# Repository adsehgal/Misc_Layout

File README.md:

<!--  -->

# \*\*

## _Requirements:_

-

## Built With

- [KiCad](https://kicad-pcb.org/) - Schematic capture and layout
- [VS Code](https://code.visualstudio.com/) - Used to develop firmware
- [Fusion 360](https://www.autodesk.com/education/edu-software/overview) - Used to design 3-D models for packages

### _Notes:_

## Authors

- **Aditya Sehgal** - _PCB Layout, Firmware, 3-D Modelling_ - [Adsehgal](https://github.com/adsehgal)

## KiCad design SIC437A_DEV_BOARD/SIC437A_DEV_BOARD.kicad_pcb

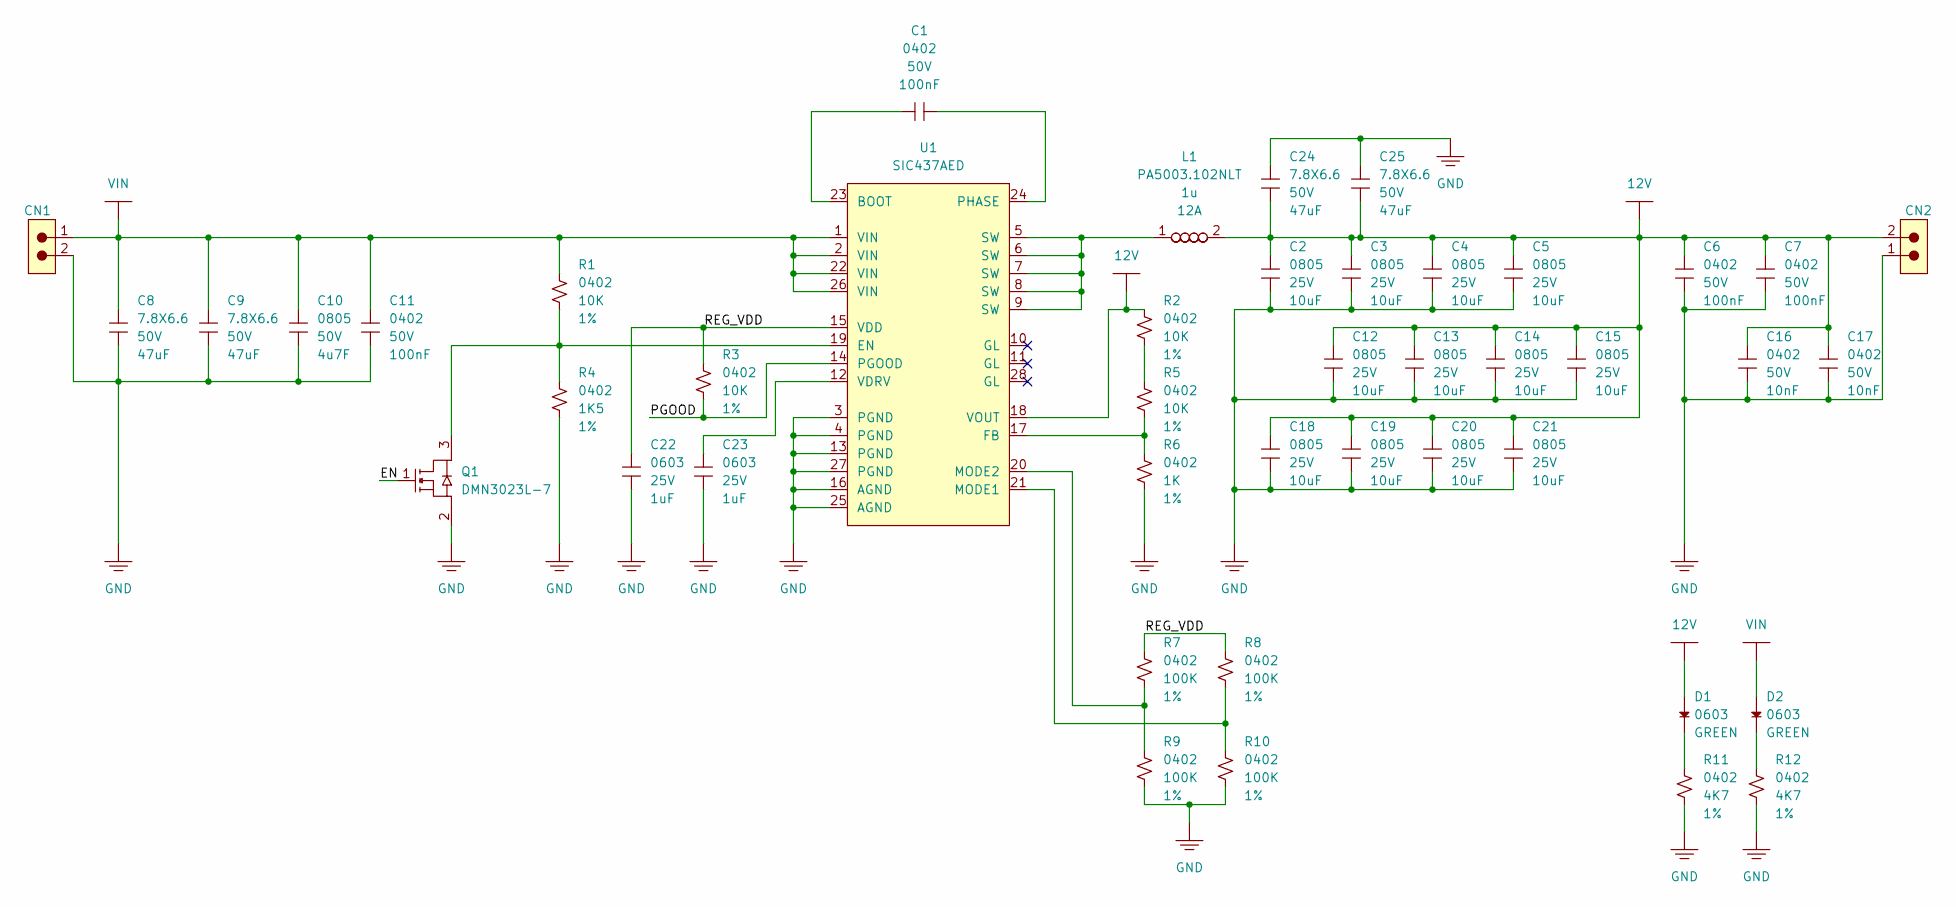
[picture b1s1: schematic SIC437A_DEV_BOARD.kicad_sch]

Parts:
C1, C6, C7, C11: Cap_100n_50V_0402; CAP_0402_LEAST; Voltage 50V; Tolerance 10%
C2, C3, C4, C5, C12, C13, C14, C15, C18, C19, C20, C21: Cap_10u_25V_0805; CAP_0805_LEAST; Voltage 25V; Tolerance 10%
C8, C9, C24, C25: Cap_47u_50V_7.8X6.6; CAP_STACK_7.8X6.6; Voltage 50V; Tolerance 20%
C10: Cap_4u7_50V_0805; CAP_0805_LEAST; Voltage 50V; Tolerance 10%
C16, C17: Cap_10n_50V_0402; CAP_0402_LEAST; Voltage 50V; Tolerance 5%
C22, C23: Cap_1u_25V_0603; CAP_0603_LEAST; Voltage 25V; Tolerance 10%
CN1, CN2: DATAMATE_2P_RA_M80-5000000M5-02-333-00-000
D1, D2: LED_GREEN_0603; LED_0603_LEAST
L1: PA5003.102NLT; IND_5.5X5.3
Q1: DMN3023L-7; SOT23_3
R1, R2, R3, R5: Res_10K_0402; RES_0402_LEAST; Tolerance 1%
R4: Res_1K5_0402; RES_0402_LEAST; Tolerance 1%
R6: Res_1K_0402; RES_0402_LEAST; Tolerance 1%
R7, R8, R9, R10: Res_100K_0402; RES_0402_LEAST; Tolerance 1%
R11, R12: Res_4K7_0402; RES_0402_LEAST; Tolerance 1%
U1: SIC437AED; MLP44_24L

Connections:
12V: C2.2, C3.2, C4.2, C5.2, C6.2, C7.2, C12.2, C13.2, C14.2, C15.2, C16.2, C17.2, C18.2, C19.2, C20.2, C21.2, C24.1, C25.1, CN2.2 (PA), D1.2, L1.2, R2.2, U1.18 (VOUT)
/EN: Q1.1
/PGOOD: R3.1, U1.14 (PGOOD)
/REG_VDD: C22.2, R3.2, R7.2, R8.2, U1.15 (VDD)
GND: C2.1, C3.1, C4.1, C5.1, C6.1, C7.1, C8.1, C9.1, C10.1, C11.1, C12.1, C13.1, C14.1, C15.1, C16.1, C17.1, C18.1, C19.1, C20.1, C21.1, C22.1, C23.1, C24.2, C25.2, CN1.2 (PA), CN2.1 (PA), Q1.2, R4.1, R6.1, R9.1, R10.1, R11.1, R12.1, U1.3 (PGND), U1.4 (PGND), U1.13 (PGND), U1.16 (AGND), U1.25 (AGND), U1.27 (PGND)
unnamed: C1.1, U1.23 (BOOT)
unnamed: C1.2, U1.24 (PHASE)
unnamed: C23.2, U1.12 (VDRV)
unnamed: D1.1, R11.2
unnamed: D2.1, R12.2
unnamed: L1.1, U1.5 (SW), U1.6 (SW), U1.7 (SW), U1.8 (SW), U1.9 (SW)
unnamed: Q1.3, R1.1, R4.2, U1.19 (EN)
unnamed: R2.1, R5.2
unnamed: R5.1, R6.2, U1.17 (FB)
unnamed: R7.1, R9.2, U1.20 (MODE2)
unnamed: R8.1, R10.2, U1.21 (MODE1)
VIN: C8.2, C9.2, C10.2, C11.2, CN1.1 (PA), D2.2, R1.2, U1.1 (VIN), U1.2 (VIN), U1.22 (VIN), U1.26 (VIN)

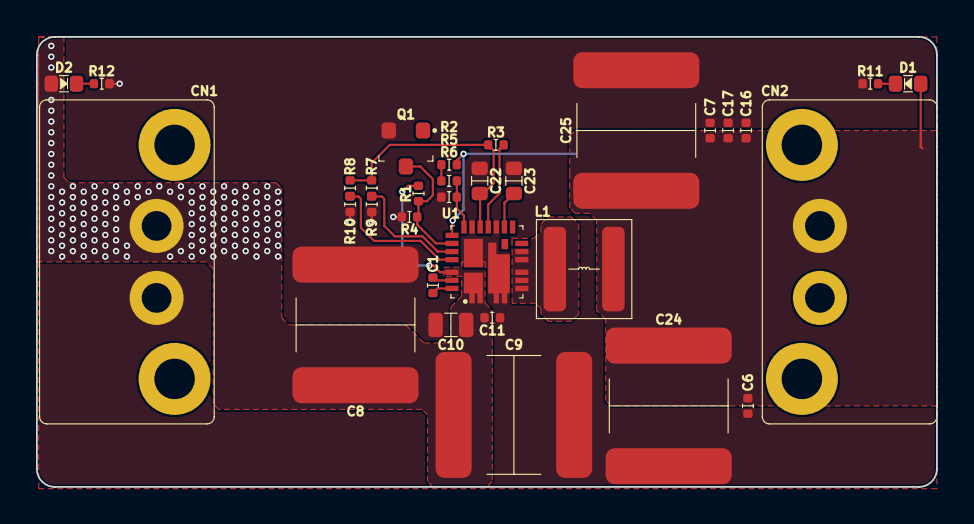
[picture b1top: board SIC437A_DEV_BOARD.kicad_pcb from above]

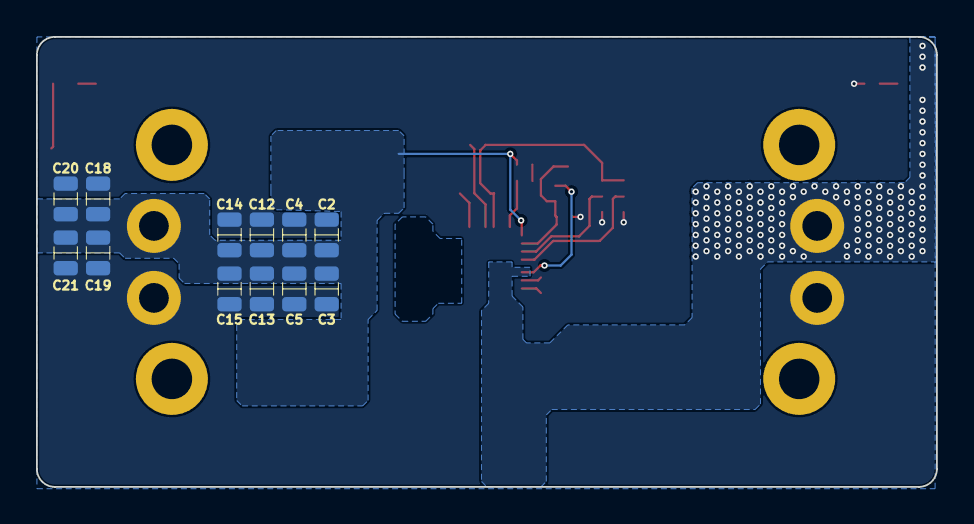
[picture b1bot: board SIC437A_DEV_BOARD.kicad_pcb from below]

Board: 4 copper layers, 50.0 x 25.0 mm, 44 parts (12 on the bottom side), 16 nets.

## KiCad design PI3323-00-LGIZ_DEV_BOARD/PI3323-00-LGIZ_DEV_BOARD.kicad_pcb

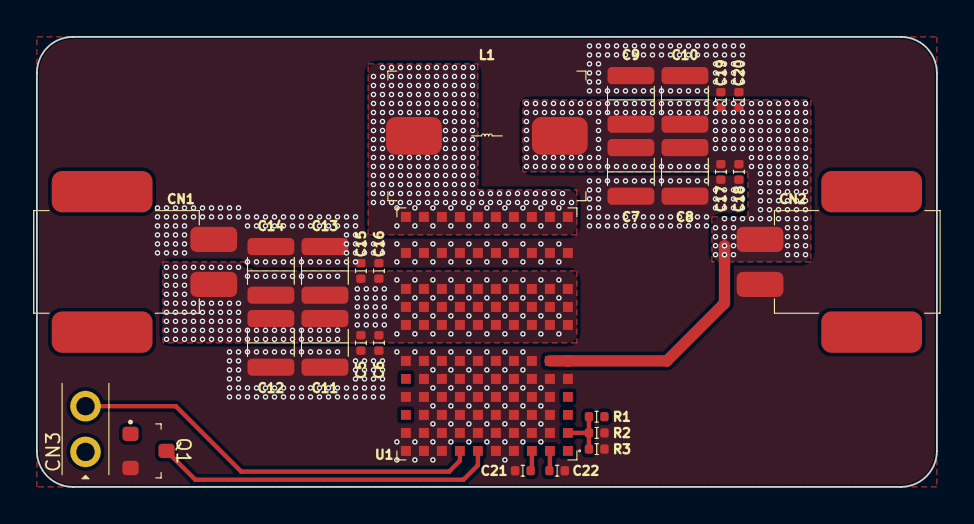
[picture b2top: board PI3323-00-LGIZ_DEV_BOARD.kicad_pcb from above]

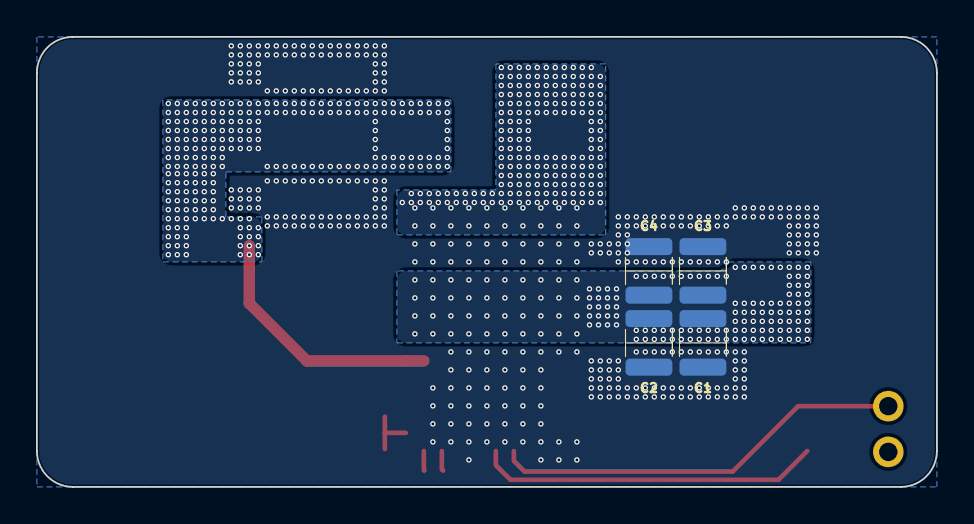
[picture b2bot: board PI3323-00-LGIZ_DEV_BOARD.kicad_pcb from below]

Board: 6 copper layers, 50.0 x 25.0 mm, 31 parts (4 on the bottom side), 11 nets.

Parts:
C1, C2, C3, C4, C11, C12, C13, C14: Cap_4u7_50V_1210; CAP_1210_LEAST
C5, C6, C15, C16, C17, C18, C19, C20: Cap_100n_50V_0402; CAP_0402_LEAST
C7, C8, C9, C10: Cap_22u_25V_1210; CAP_1210_LEAST
C21, C22: Cap_10n_50V_0402; CAP_0402_LEAST
CN1, CN2: SCREW_TERMINAL_2P_RA_1702473
CN3: 1x2Pos_100MIL_THT; 1x2_Pos_100MIL_THT
L1: FP1107R1-R23-R; IND_11X7.2
Q1: DMN3300U-7; SOT23_3
R1: Res_1K_0402; RES_0402_LEAST
R2, R3: Res_4K7_0402; RES_0402_LEAST
U1: PI3323-00-LGIZ; LGA110_10X14

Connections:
3V3: C7.2, C8.2, C9.2, C10.2, C17.2, C18.2, C19.2, C20.2, CN2.2 (PA), L1.2, R1.2, U1.A6 (VOUT), U1.B6 (VOUT)
/ENABLE: CN3.1 (PA), Q1.1
/PWRGD: CN3.2 (PA), U1.G1 (PWRGD)
GND: C1.1, C2.1, C3.1, C4.1, C5.1, C6.1, C7.1, C8.1, C9.1, C10.1, C11.1, C12.1, C13.1, C14.1, C15.1, C16.1, C17.1, C18.1, C19.1, C20.1, C21.1, C22.1, CN1.1 (PA), CN2.1 (PA), Q1.2, R2.1, R3.1, U1.A5 (VSP), U1.A12 (PGND), U1.B2 (SGND), U1.B3 (SGND), U1.B4 (SGND), U1.B5 (PGND), U1.B12 (PGND), U1.C2 (SGND), U1.C3 (SGND), U1.C4 (PGND), U1.C5 (PGND), U1.C6 (PGND), U1.C12 (PGND), U1.D1 (SGND), U1.D2 (SGND), U1.D3 (SGND), U1.D4 (PGND), U1.D5 (PGND), U1.D6 (PGND), U1.D12 (PGND), U1.E1 (TEST5), U1.E2 (SGND), U1.E3 (SGND), U1.E4 (PGND), U1.E5 (PGND), U1.E6 (PGND), U1.E12 (PGND), U1.F2 (PGND), U1.F3 (PGND), U1.F4 (PGND), U1.F5 (PGND), U1.F6 (PGND), U1.F12 (PGND), U1.G2 (PGND), U1.G3 (PGND), U1.G4 (PGND), U1.G5 (PGND), U1.G6 (PGND), U1.G12 (PGND), U1.H1 (TEST4), U1.H2 (PGND), U1.H3 (PGND), U1.H4 (PGND), U1.H5 (PGND), U1.H6 (PGND), U1.H12 (PGND), U1.J1 (TEST3), U1.J2 (PGND), U1.J3 (PGND), U1.J4 (PGND), U1.J5 (PGND), U1.J6 (PGND), U1.J12 (PGND), U1.K1 (TEST2), U1.K2 (TEST1), U1.K4 (SYNCI), U1.K6 (PGND), U1.K12 (PGND)
unnamed: C21.2, U1.C1 (TRK)
unnamed: C22.2, U1.B1 (COMP)
unnamed: L1.1, U1.A14 (VS1), U1.B14 (VS1), U1.C14 (VS1), U1.D14 (VS1), U1.E14 (VS1), U1.F14 (VS1), U1.G14 (VS1), U1.H14 (VS1), U1.J14 (VS1), U1.K14 (VS1)
unnamed: Q1.3, U1.F1 (EN)
unnamed: R1.1, R2.2, R3.2, U1.A2 (EAIN)
unnamed: U1.A3 (VDIFF), U1.A4 (VSN)
VDD: C1.2, C2.2, C3.2, C4.2, C5.2, C6.2, C11.2, C12.2, C13.2, C14.2, C15.2, C16.2, CN1.2 (PA), U1.A8 (VIN), U1.A9 (VIN), U1.A10 (VIN), U1.B8 (VIN), U1.B9 (VIN), U1.B10 (VIN), U1.C8 (VIN), U1.C9 (VIN), U1.C10 (VIN), U1.D8 (VIN), U1.D9 (VIN), U1.D10 (VIN), U1.E8 (VIN), U1.E9 (VIN), U1.E10 (VIN), U1.F8 (VIN), U1.F9 (VIN), U1.F10 (VIN), U1.G8 (VIN), U1.G9 (VIN), U1.G10 (VIN), U1.H8 (VIN), U1.H9 (VIN), U1.H10 (VIN), U1.J8 (VIN), U1.J9 (VIN), U1.J10 (VIN), U1.K8 (VIN), U1.K9 (VIN), U1.K10 (VIN)

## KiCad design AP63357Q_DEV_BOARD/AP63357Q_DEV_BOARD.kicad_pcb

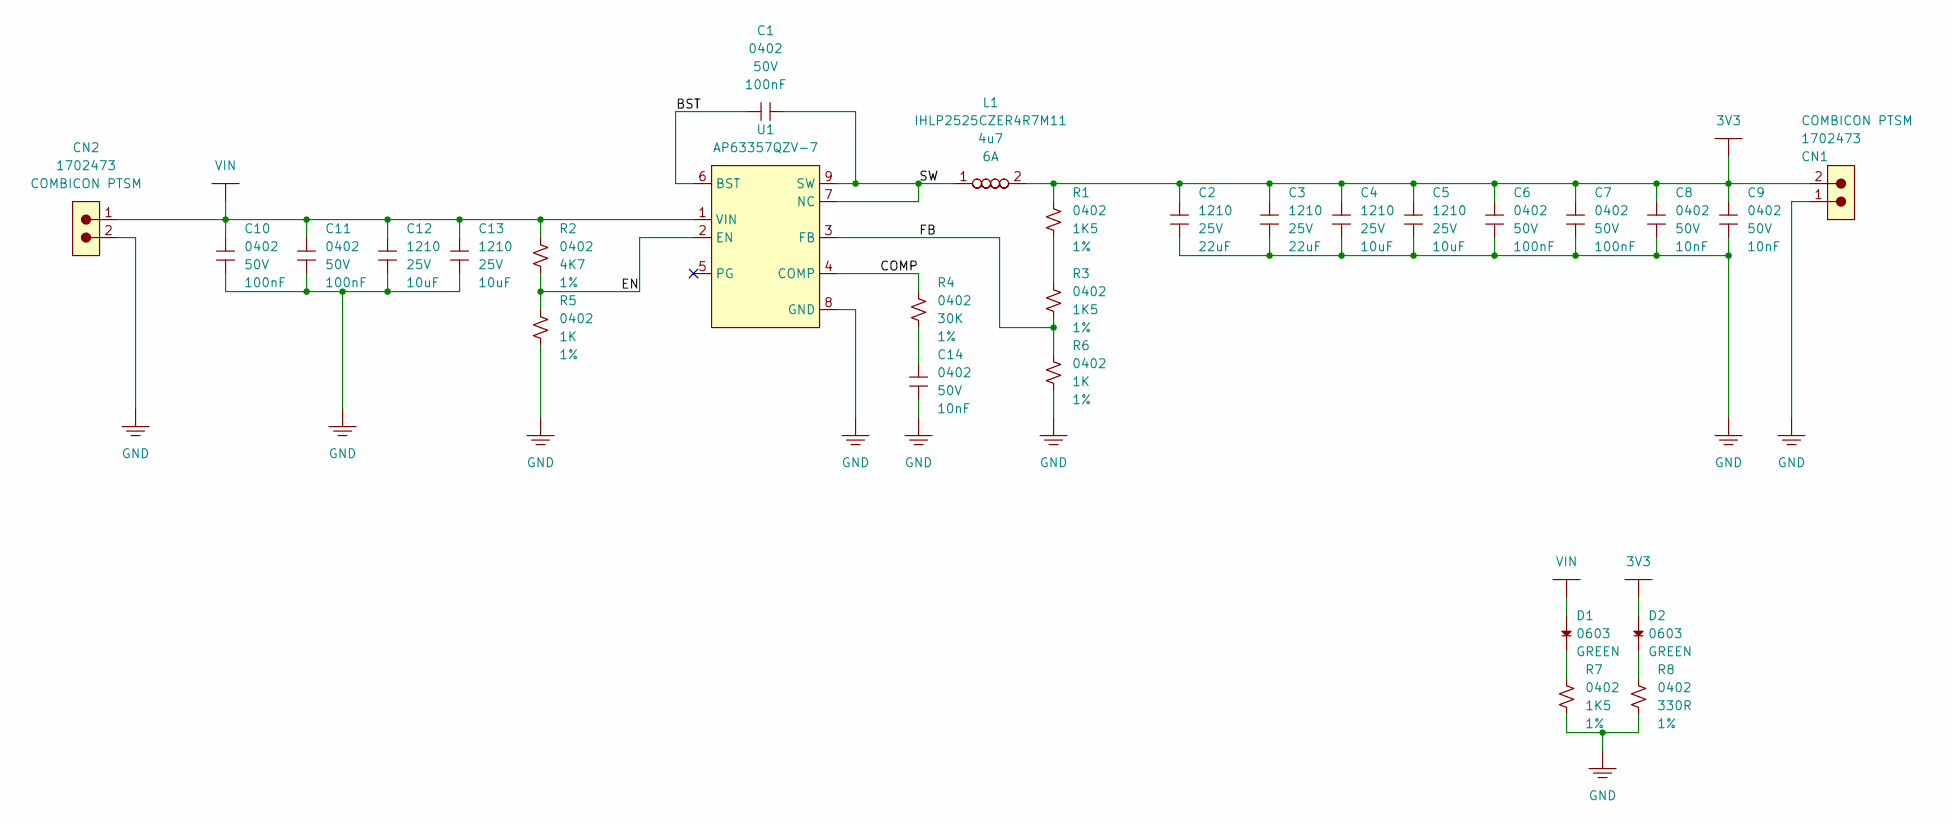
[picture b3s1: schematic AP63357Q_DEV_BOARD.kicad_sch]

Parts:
C1, C6, C7, C10, C11: Cap_100n_50V_0402; CAP_0402_LEAST; Voltage 50V; Tolerance 10%
C2, C3: Cap_22u_25V_1210; CAP_1210_LEAST; Voltage 25V; Tolerance 10%
C4, C5, C12, C13: Cap_10u_25V_1210; CAP_1210_LEAST; Voltage 25V; Tolerance 10%
C8, C9, C14: Cap_10n_50V_0402; CAP_0402_LEAST; Voltage 50V; Tolerance 5%
CN1, CN2: SCREW_TERMINAL_2P_RA_1702473
D1, D2: LED_GREEN_0603; LED_0603_LEAST
L1: IHLP2525CZER4R7M11; IND_6.5X6.5
R1, R3, R7: Res_1K5_0402; RES_0402_LEAST; Tolerance 1%
R2: Res_4K7_0402; RES_0402_LEAST; Tolerance 1%
R4: Res_30K_0402; RES_0402_LEAST; Tolerance 1%
R5, R6: Res_1K_0402; RES_0402_LEAST; Tolerance 1%
R8: Res_330_0402; RES_0402_LEAST; Tolerance 1%
U1: AP63357QZV; VDFN3020-13-DiodeInc

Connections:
3V3: C2.2, C3.2, C4.2, C5.2, C6.2, C7.2, C8.2, C9.2, CN1.2 (PA), D2.2, L1.2, R1.2
/BST: C1.1, U1.6 (BST)
/COMP: R4.2, U1.4 (COMP)
/EN: R2.1, R5.2, U1.2 (EN)
/FB: R3.1, R6.2, U1.3 (FB)
/SW: C1.2, L1.1, U1.7 (NC), U1.9 (SW)
GND: C2.1, C3.1, C4.1, C5.1, C6.1, C7.1, C8.1, C9.1, C10.1, C11.1, C12.1, C13.1, C14.1, CN1.1 (PA), CN2.2 (PA), R5.1, R6.1, R7.1, R8.1, U1.8 (GND)
unnamed: C14.2, R4.1
unnamed: D1.1, R7.2
unnamed: D2.1, R8.2
unnamed: R1.1, R3.2
VIN: C10.2, C11.2, C12.2, C13.2, CN2.1 (PA), D1.2, R2.2, U1.1 (VIN)

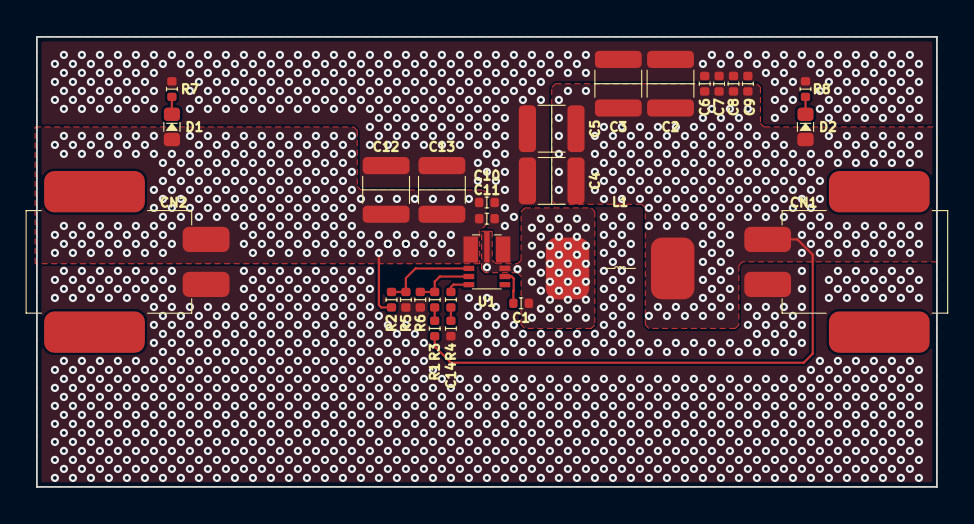
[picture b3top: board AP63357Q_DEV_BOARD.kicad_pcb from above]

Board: 6 copper layers, 50.0 x 25.0 mm, 28 parts (0 on the bottom side), 12 nets.

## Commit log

2022-06-30 repo init
2022-10-07 Added boards for SIC437, PI3323 and AP63357
